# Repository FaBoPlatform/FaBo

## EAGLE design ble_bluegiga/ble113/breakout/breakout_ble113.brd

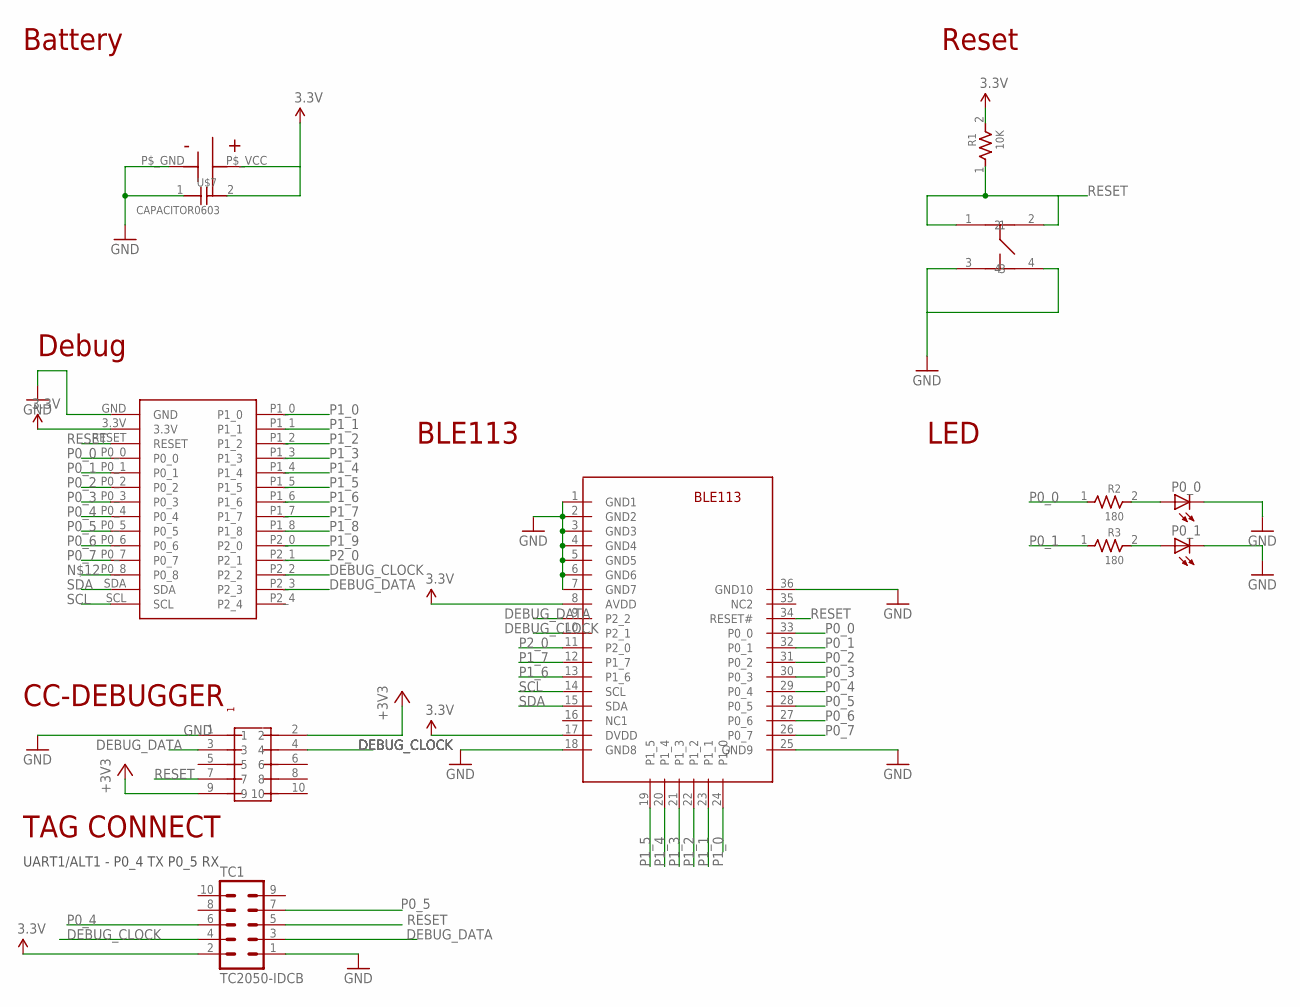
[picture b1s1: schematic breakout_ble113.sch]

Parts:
P0_0, P0_1: LEDCHIP-LED0603; CHIP-LED0603
R1: 10K; 0603
R2, R3: 180; 0603
TC1: TC2050-IDCB; TC2050-IDC
U$1: PIN-HEADER-SMT(1.27MM)2X5
U$2: BREAKOUT_BLE
U$3: BLUEGIGA-BLE113
U$4: SMTU2450-TOP; SMTU2450
U$5: SWICTH-4P(KMR2); SWITCH-4P(KMR2)
U$7: CAPACITOR0603; 0603

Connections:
3.3V: R1.2, TC1.2, U$2.3.3V, U$3.8 (AVDD), U$3.17 (DVDD), U$4.P$_VCC (+), U$7.2
+3V3: U$1.2, U$1.9
DEBUG_CLOCK: TC1.4, U$1.4, U$2.P2_2, U$3.10 (P2_1)
DEBUG_DATA: TC1.3, U$1.3, U$2.P2_3, U$3.9 (P2_2)
GND: P0_0.C, P0_1.C, TC1.1, U$1.1, U$2.GND, U$3.1 (GND1), U$3.2 (GND2), U$3.3 (GND3), U$3.4 (GND4), U$3.5 (GND5), U$3.6 (GND6), U$3.7 (GND7), U$3.18 (GND8), U$3.25 (GND9), U$3.36 (GND10), U$4.P$_GND (-), U$5.3, U$5.4, U$7.1
P0_0: R2.1, U$2.P0_0, U$3.33 (P0_0)
P0_1: R3.1, U$2.P0_1, U$3.32 (P0_1)
P0_2: U$2.P0_2, U$3.31 (P0_2)
P0_3: U$2.P0_3, U$3.30 (P0_3)
P0_4: TC1.6, U$2.P0_4, U$3.29 (P0_4)
P0_5: TC1.7, U$2.P0_5, U$3.28 (P0_5)
P0_6: U$2.P0_6, U$3.27 (P0_6)
P0_7: U$2.P0_7, U$3.26 (P0_7)
P1_0: U$2.P1_0, U$3.24 (P1_0)
P1_1: U$2.P1_1, U$3.23 (P1_1)
P1_2: U$2.P1_2, U$3.22 (P1_2)
P1_3: U$2.P1_3, U$3.21 (P1_3)
P1_4: U$2.P1_4, U$3.20 (P1_4)
P1_5: U$2.P1_5, U$3.19 (P1_5)
P1_6: U$2.P1_6, U$3.13 (P1_6)
P1_7: U$2.P1_7, U$3.12 (P1_7)
P1_8: U$2.P1_8
P1_9: U$2.P2_0
P2_0: U$2.P2_1, U$3.11 (P2_0)
R1: P0_1.A, R3.2
R2: P0_0.A, R2.2
RESET: R1.1, TC1.5, U$1.7, U$2.RESET, U$3.34 (RESET#), U$5.1, U$5.2
SCL: U$2.SCL, U$3.14 (SCL)
SDA: U$2.SDA, U$3.15 (SDA)

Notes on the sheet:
Reset
Battery
Debug
BLE113
LED
UART1/ALT1 - P0_4 TX P0_5 RX
TAG CONNECT
CC-DEBUGGER

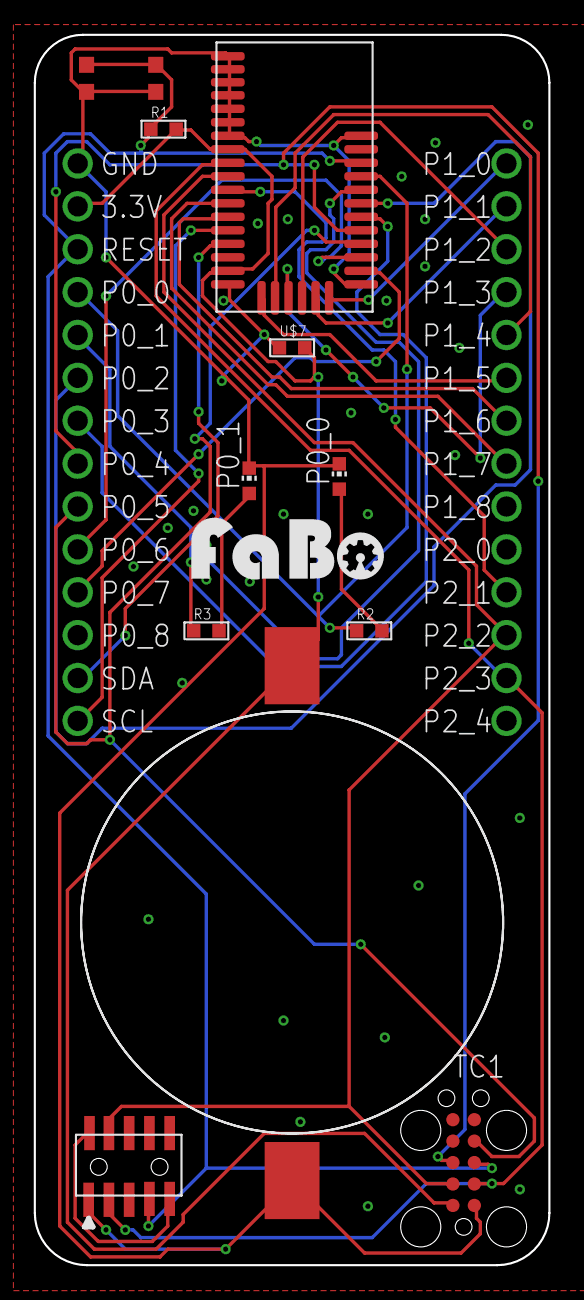
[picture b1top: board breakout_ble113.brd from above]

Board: 2 copper layers, 30.5 x 72.9 mm, 13 parts (0 on the bottom side), 27 nets.

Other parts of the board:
U$8: LOGO_FABO_M

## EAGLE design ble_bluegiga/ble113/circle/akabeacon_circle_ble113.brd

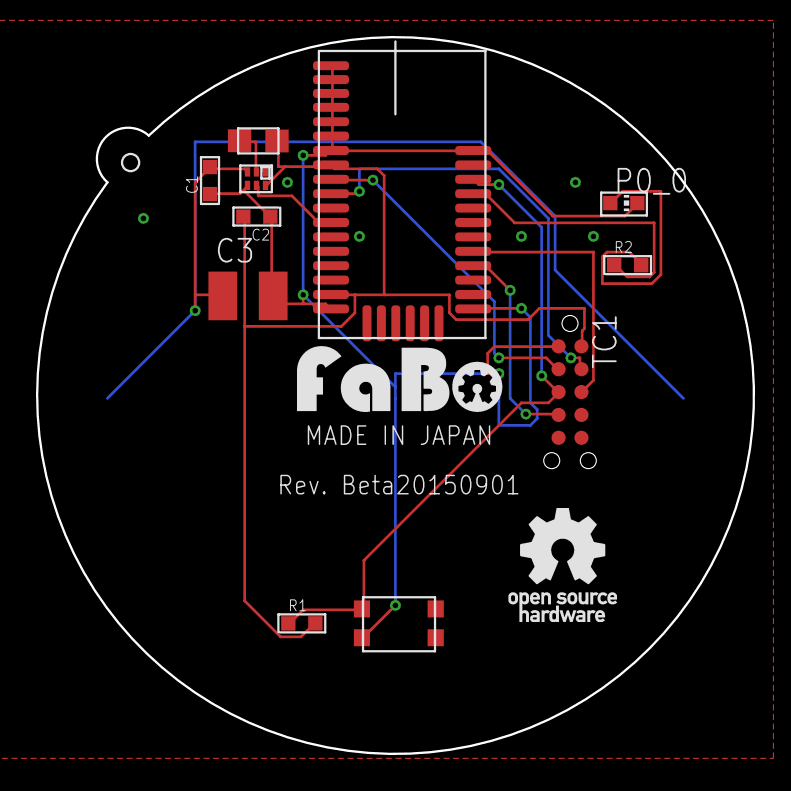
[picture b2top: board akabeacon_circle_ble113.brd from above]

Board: 2 copper layers, 39.8 x 39.8 mm, 14 parts (0 on the bottom side), 12 nets.

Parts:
C1, C2: CAPACITOR0603; 0603
C3: C3225
I1: INDUCTOR-0805
P0_0: CHIP-LED0603
R1: 10K; 0603
R2: 180; 0603
TC1: TC2050-IDC; TC2050-IDC-NL
TPS1: TI-TPS62730
U$1: CIRCLE-TYPE1; CIRCLE-TYE1-TC2030
U$2: LOGO_FABO_M
U$4: BLE113
U$5: SWICTH-4P(KMR2); SWITCH-4P(KMR2)
U$7: LOGO_OSHW_T_M

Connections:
3.3V: C2.2, I1.P$2, R1.2, TC1.2, TPS1.6, U$4.8, U$4.17
DEBUG_CLOCK: TC1.4, U$4.10
DEBUG_DATA: TC1.3, U$4.9
GND: C1.1, C2.1, C3.2, P0_0.C, TC1.1, TPS1.4, U$1.GND, U$4.1, U$4.2, U$4.3, U$4.4, U$4.5, U$4.6, U$4.7, U$4.18, U$4.25, U$4.36, U$5.3
unnamed: C1.2, C3.1, TPS1.3, U$1.PLUS1, U$1.PLUS2
unnamed: I1.P$1, TPS1.2
P0_0: R2.1, U$4.33
P0_4: TC1.6, U$4.29
P0_5: TC1.7, U$4.28
P1_7: TPS1.5, U$4.12
R2: P0_0.A, R2.2
RESET: R1.1, TC1.5, U$4.34, U$5.1

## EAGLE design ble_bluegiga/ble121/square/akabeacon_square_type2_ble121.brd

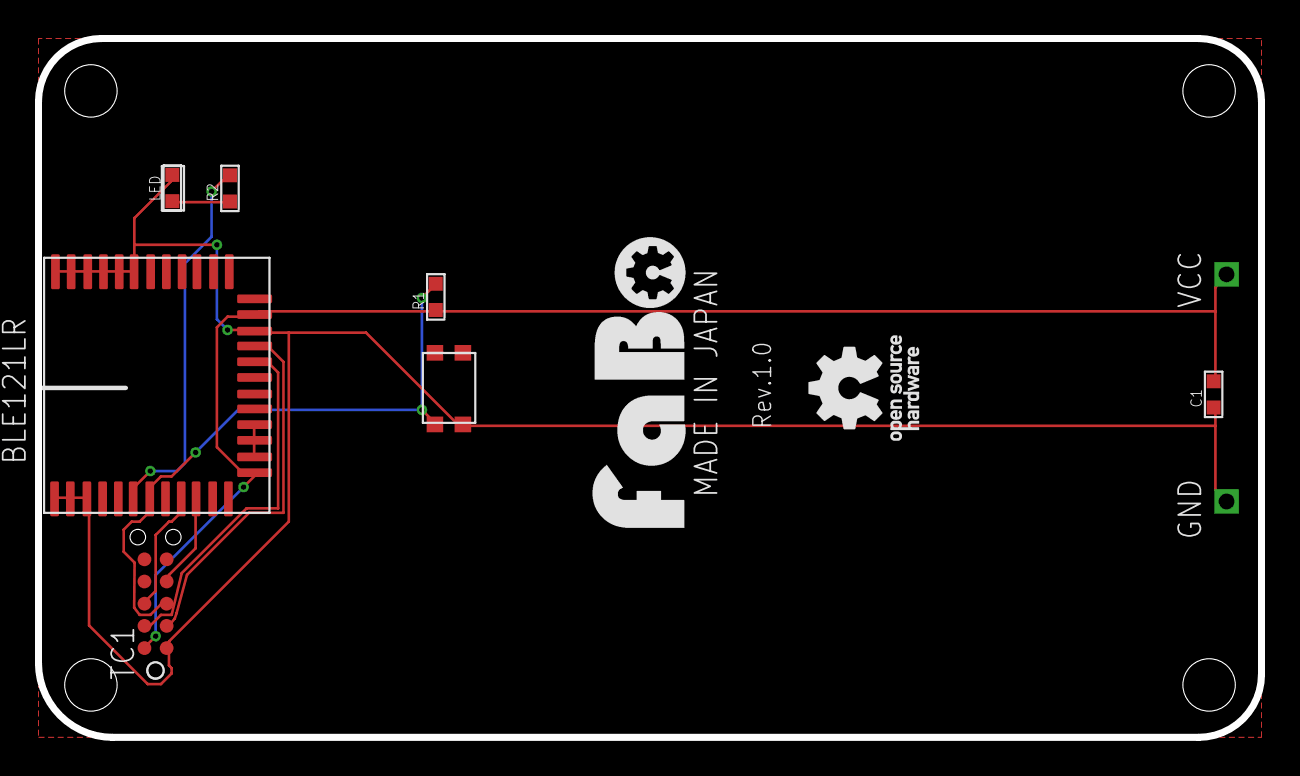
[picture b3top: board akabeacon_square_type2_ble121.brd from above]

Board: 2 copper layers, 70.0 x 40.0 mm, 8 parts (0 on the bottom side), 10 nets.

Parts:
BLE1: BLUEGIGA-BLE121LR
C1: 1u; 0603
LED: LED0603; 0603
R1, R2: 4.7K; 0603
TC1: TC2050-IDC; TC2050-IDC-NL
U$2: SQUARE-TYPE2-TC2050
U$6: SWICTH-4P(KMR2); SWITCH-4P(KMR2)

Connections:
3.3V: BLE1.13, BLE1.23, C1.2, R1.1, TC1.2, U$2.VCC
DEBUG_CLOCK: BLE1.20, TC1.4
DEBUG_DATA: BLE1.21, TC1.3
GND: BLE1.1, BLE1.2, BLE1.3, BLE1.22, BLE1.31, BLE1.32, BLE1.33, BLE1.34, BLE1.35, BLE1.36, C1.1, LED.CATHODE, TC1.1, U$2.GND, U$6.3
unnamed: LED.ANODE, R2.1
unnamed: BLE1.14, BLE1.15, BLE1.16
P0_0: BLE1.6, R2.2
P0_4: BLE1.9, TC1.6
P0_5: BLE1.10, TC1.7
RESET: BLE1.7, R1.2, TC1.5, U$6.1

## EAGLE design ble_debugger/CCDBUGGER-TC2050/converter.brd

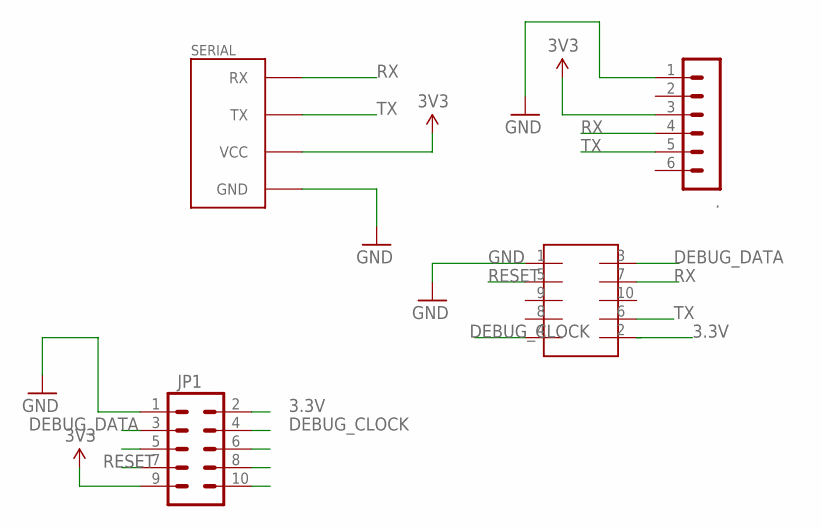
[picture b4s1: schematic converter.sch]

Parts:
.: MA06-1
JP1: M05X2SHD; 2X5-SHROUDED
SERIAL: FABO_BRICK_SERIAL-CONNECTOR_I; FABO_BRICK_SERIAL_CONNECTOR_I
U$4: TC-2050-SOCKET

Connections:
3.3V: JP1.2, U$4.2
3V3: ..3, JP1.9, SERIAL.VCC
CSN: JP1.5
DEBUG_CLOCK: JP1.4, U$4.4
DEBUG_DATA: JP1.3, U$4.3
GND: ..1, JP1.1, SERIAL.GND, U$4.1
MISO: JP1.10
MOSI: JP1.8
RESET: JP1.7, U$4.5
RX: ..4, SERIAL.RX, U$4.7
SCLK: JP1.6
TX: ..5, SERIAL.TX, U$4.6

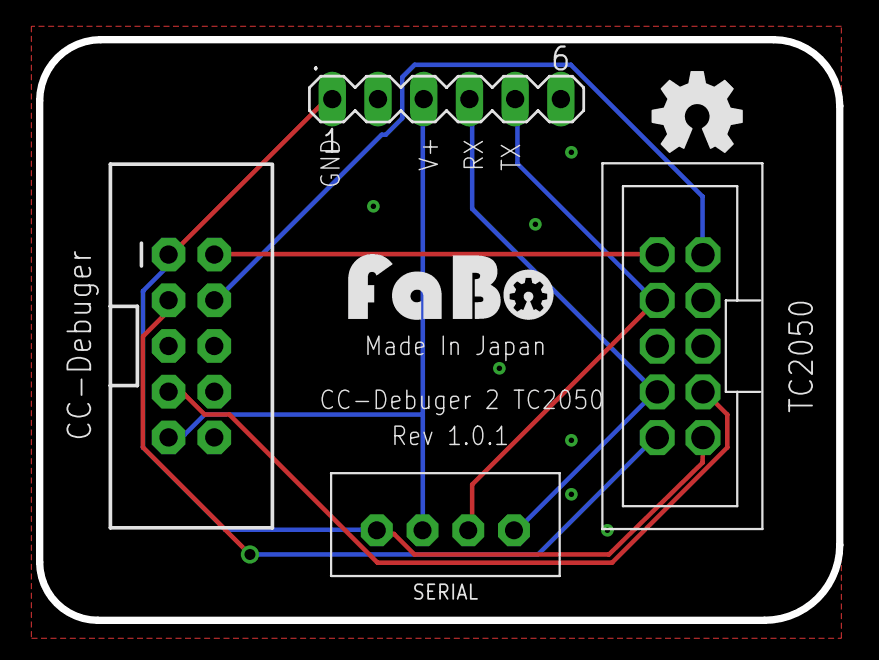
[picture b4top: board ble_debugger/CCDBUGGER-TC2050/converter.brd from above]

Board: 2 copper layers, 44.4 x 32.3 mm, 6 parts (0 on the bottom side), 8 nets.

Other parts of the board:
U$1: LOGO_FABO_M
U$2: LOGO_OSHW_M

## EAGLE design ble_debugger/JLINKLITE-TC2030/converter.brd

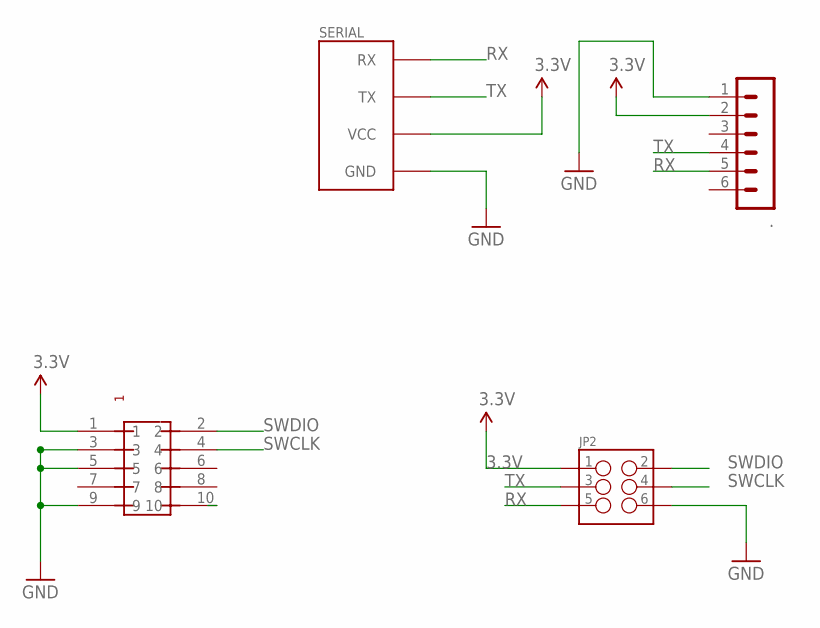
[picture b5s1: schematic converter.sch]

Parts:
.: MA06-1
JP2: M03X2; 2X3-SHROUDED
SERIAL: FABO_BRICK_SERIAL-CONNECTOR_I; FABO_BRICK_SERIAL_CONNECTOR_I
U$5: PIN-HEADER-SMT(1.27MM)2X5

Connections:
3.3V: ..2, JP2.1, SERIAL.VCC, U$5.1
GND: ..1, JP2.6, SERIAL.GND, U$5.3, U$5.5, U$5.9
RESET: U$5.10
RX: ..5, JP2.5, SERIAL.RX
SWCLK: JP2.4, U$5.4
SWDIO: JP2.2, U$5.2
TX: ..4, JP2.3, SERIAL.TX

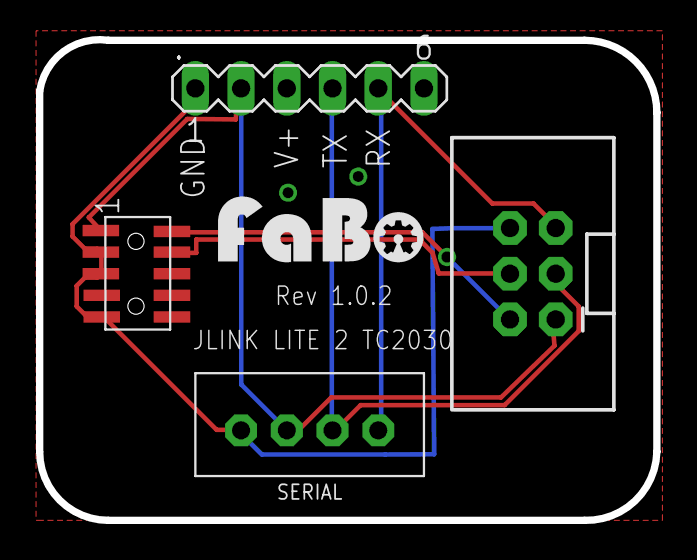
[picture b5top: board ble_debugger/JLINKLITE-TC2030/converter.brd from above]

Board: 2 copper layers, 34.3 x 26.7 mm, 5 parts (0 on the bottom side), 6 nets.

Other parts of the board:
U$1: LOGO_FABO_M

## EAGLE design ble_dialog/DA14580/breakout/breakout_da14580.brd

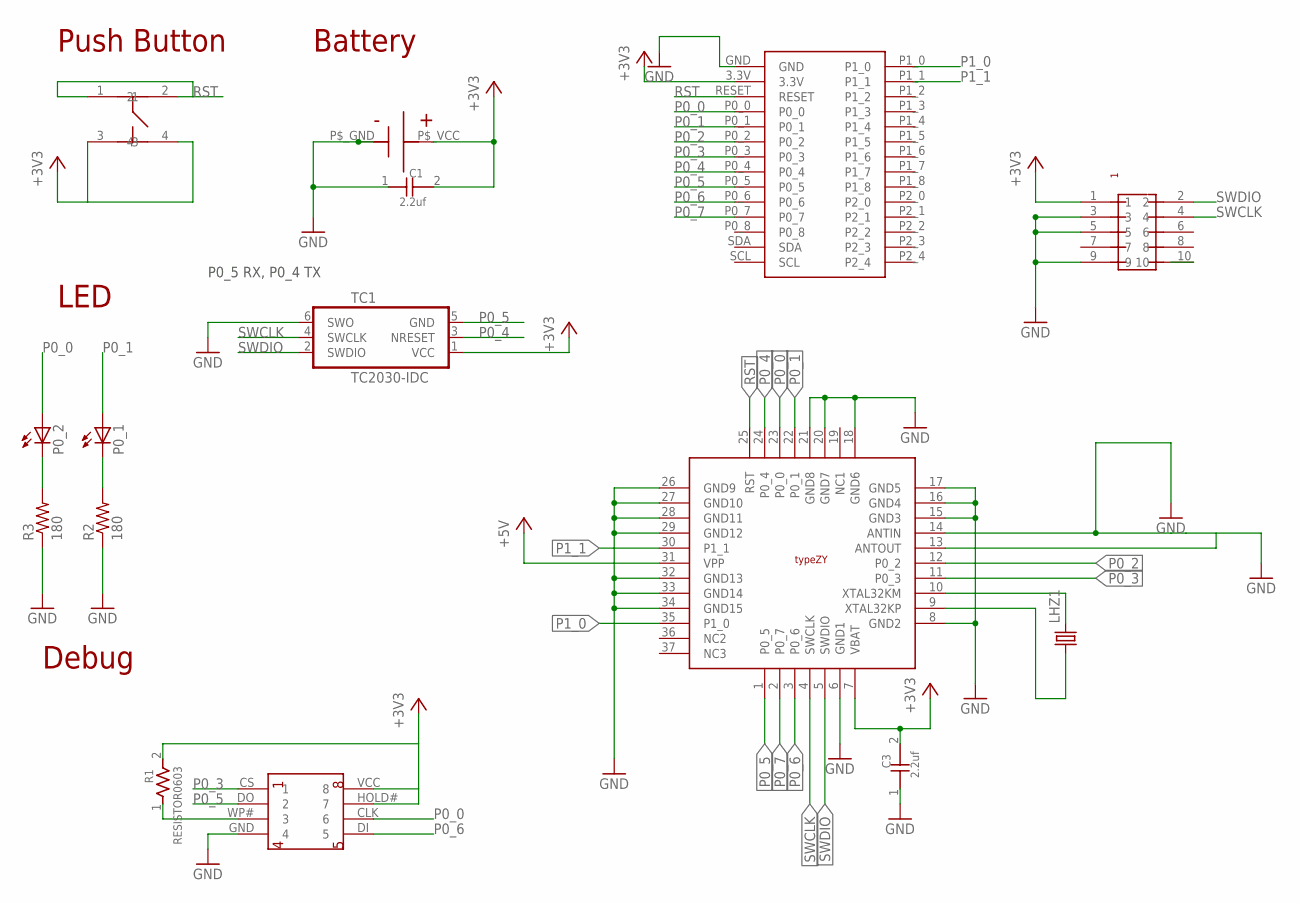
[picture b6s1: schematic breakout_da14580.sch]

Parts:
C1, C3: 2.2uf; 0603
LHZ1: FC-12M
P0_1, P0_2: LEDCHIP-LED0603; CHIP-LED0603
R1: RESISTOR0603; 0603
R2, R3: 180; 0603-RES
TC1: TC2030-IDC
U$1: MURATA-TYPEZY; MURATA_TYPEZY
U$2: BREAKOUT_BLE
U$3: SMTU2450-TOP; SMTU2450
U$5: FLASH-MEMORY-2M(WINBOND)
U$6: PIN-HEADER-SMT(1.27MM)2X5
U$7: SWICTH-4P(KMR2); SWITCH-4P(KMR2)

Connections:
+3V3: C1.2, C3.2, R1.2, TC1.1 (VCC), U$1.7 (VBAT), U$2.3.3V, U$3.P$_VCC (+), U$5.HOLD# (7), U$5.VCC (8), U$6.1, U$7.3, U$7.4
+5V: U$1.31 (VPP)
GND: C1.1, C3.1, R2.1, R3.1, TC1.6 (SWO), U$1.6 (GND1), U$1.8 (GND2), U$1.14 (ANTIN), U$1.15 (GND3), U$1.16 (GND4), U$1.17 (GND5), U$1.18 (GND6), U$1.20 (GND7), U$1.21 (GND8), U$1.26 (GND9), U$1.27 (GND10), U$1.28 (GND11), U$1.29 (GND12), U$1.32 (GND13), U$1.33 (GND14), U$1.34 (GND15), U$2.GND, U$3.P$_GND (-), U$5.GND (4), U$6.3, U$6.5, U$6.9
LED1: P0_1.C, R2.2
LED2: P0_2.C, R3.2
unnamed: R1.1, U$5.WP# (3)
P0_0: P0_2.A, U$1.23 (P0_0), U$2.P0_0, U$5.CLK (6)
P0_1: P0_1.A, U$1.22 (P0_1), U$2.P0_1
P0_2: U$1.12 (P0_2), U$2.P0_2
P0_3: U$1.11 (P0_3), U$2.P0_3, U$5.CS (1)
P0_4: TC1.3 (NRESET), U$1.24 (P0_4), U$2.P0_4
P0_5: TC1.5 (GND), U$1.1 (P0_5), U$2.P0_5, U$5.DO (2)
P0_6: U$1.3 (P0_6), U$2.P0_6, U$5.DI (5)
P0_7: U$1.2 (P0_7), U$2.P0_7
P1_0: U$1.35 (P1_0), U$2.P1_0
P1_1: U$1.30 (P1_1), U$2.P1_1
RESET: U$6.10
RST: U$1.25 (RST), U$2.RESET, U$7.1, U$7.2
SWCLK: TC1.4 (SWCLK), U$1.4 (SWCLK), U$6.4
SWDIO: TC1.2 (SWDIO), U$1.5 (SWDIO), U$6.2
XTAL32KM: LHZ1.2, U$1.10 (XTAL32KM)
XTAL32KP: LHZ1.1, U$1.9 (XTAL32KP)

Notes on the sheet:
Battery
Push Button
Debug
LED
P0_5 RX, P0_4 TX

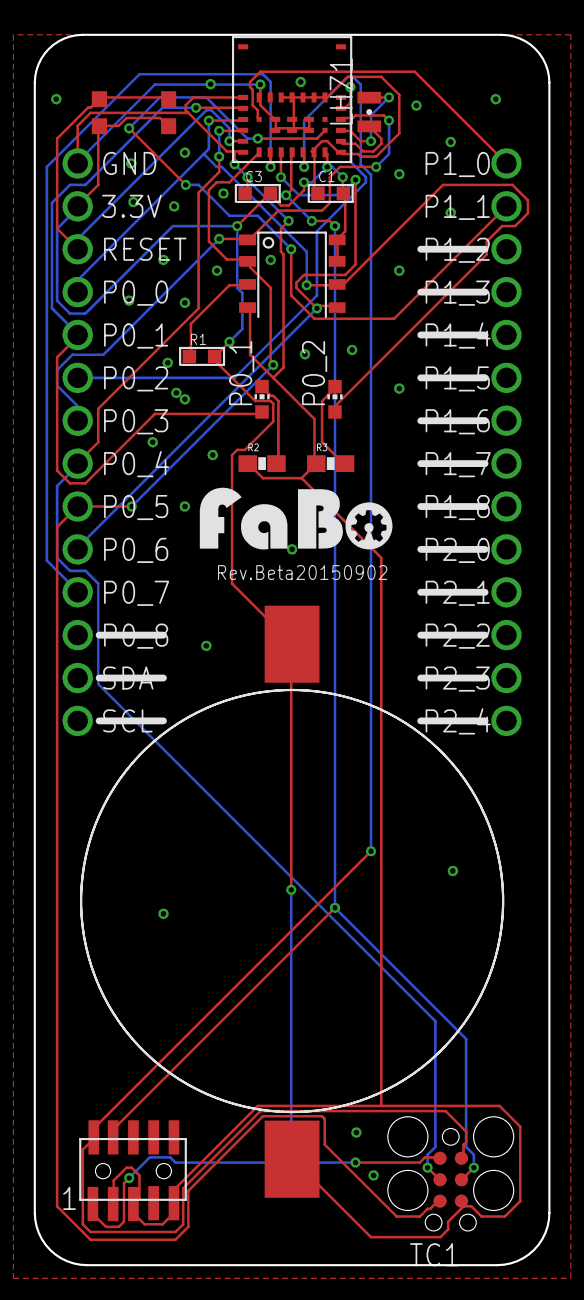
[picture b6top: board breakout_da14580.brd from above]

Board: 2 copper layers, 30.5 x 72.9 mm, 16 parts (0 on the bottom side), 20 nets.

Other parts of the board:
U$8: LOGO_FABO_M

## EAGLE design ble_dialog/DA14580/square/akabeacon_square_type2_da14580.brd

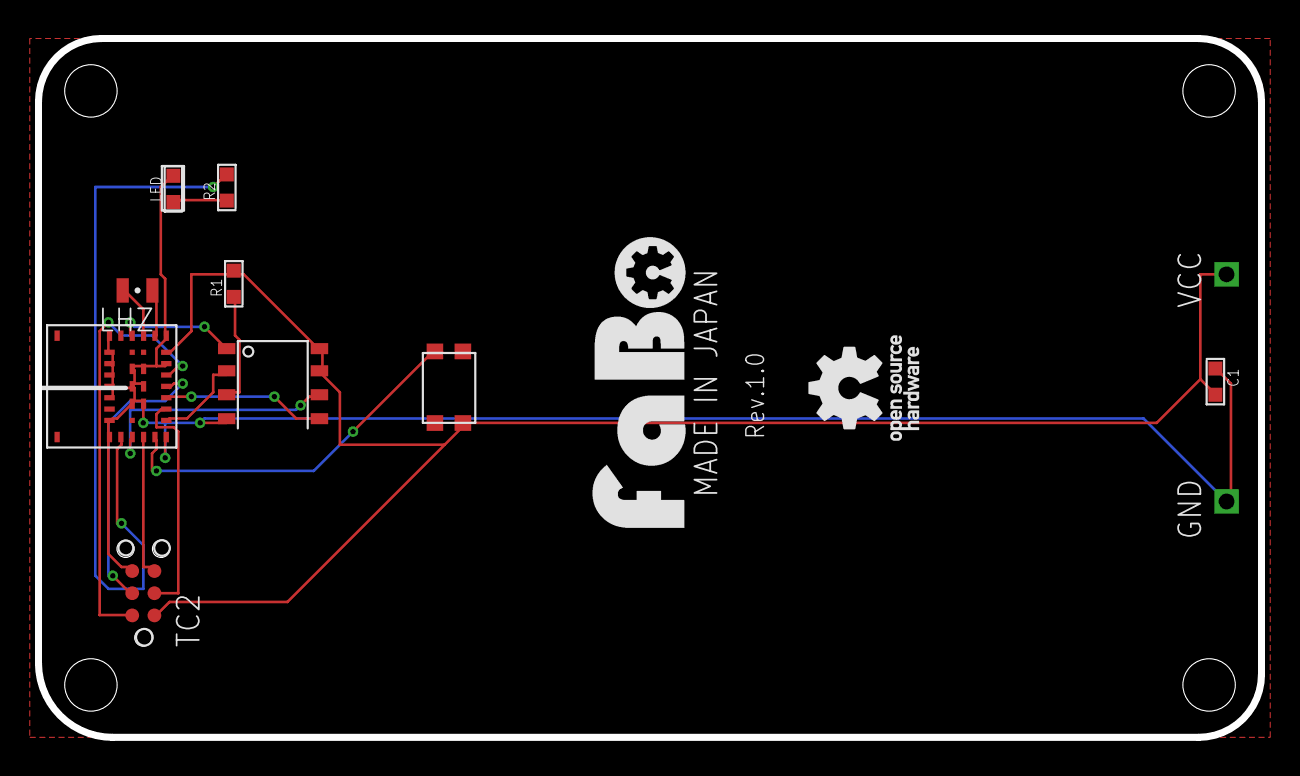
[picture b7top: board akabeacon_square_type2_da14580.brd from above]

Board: 2 copper layers, 70.0 x 40.0 mm, 10 parts (0 on the bottom side), 16 nets.

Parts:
C1: 2.2uf; 0603
LED: LED0603; 0603
LHZ: FC-12M
R1: RESISTOR0603; 0603
R2: 4.7K; 0603
TC2: TC2030-IDC-NL
U$3: FLASH-MEMORY-2M(WINBOND)
U$5: SQUARE-TYPE2-TC2030
U$7: SWICTH-4P(KMR2); SWITCH-4P(KMR2)
U$9: MURATA-TYPEZY; MURATA_TYPEZY

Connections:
+3V3: C1.2, R1.2, TC2.1, U$3.HOLD#, U$3.VCC, U$5.VCC, U$7.3, U$9.7
GND: C1.1, LED.CATHODE, TC2.6, U$3.GND, U$5.GND, U$9.6, U$9.8, U$9.13, U$9.14, U$9.15, U$9.16, U$9.17, U$9.18, U$9.20, U$9.21, U$9.26, U$9.27, U$9.28, U$9.29, U$9.32, U$9.33, U$9.34
unnamed: R1.1, U$3.WP#
unnamed: LED.ANODE, R2.1
P0_0: U$3.CLK, U$9.23
P0_1: R2.2, U$9.22
P0_3: U$3.CS, U$9.11
P0_4: TC2.5, U$9.24
P0_5: U$3.DO, U$9.1
P0_6: U$3.DI, U$9.3
P0_7: TC2.3, U$9.2
RST: U$7.2, U$9.25
SWCLK: TC2.4, U$9.4
SWDIO: TC2.2, U$9.5
XTAL32KM: LHZ.2, U$9.10
XTAL32KP: LHZ.1, U$9.9

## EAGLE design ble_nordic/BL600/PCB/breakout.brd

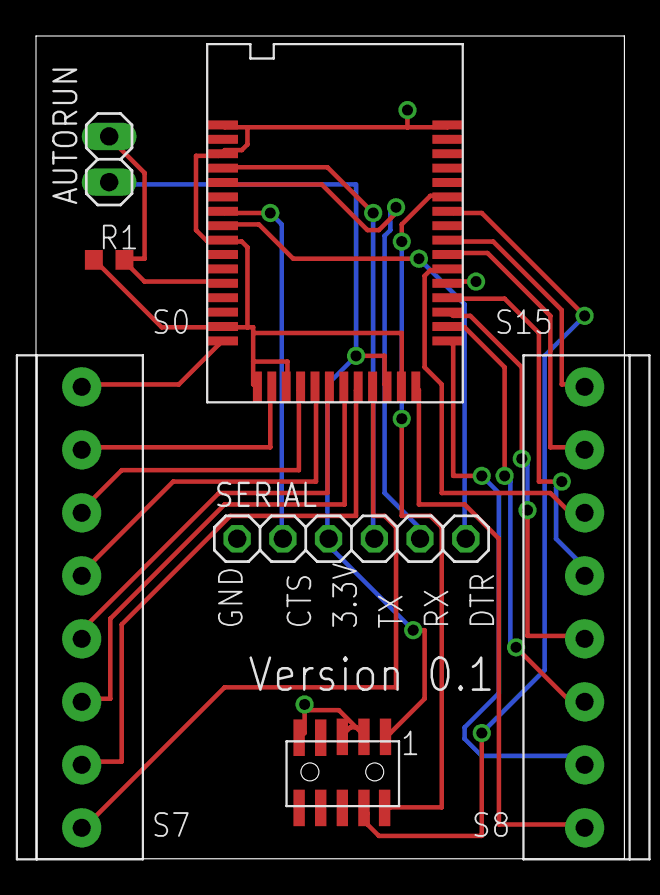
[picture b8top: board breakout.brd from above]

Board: 2 copper layers, 32.7 x 45.7 mm, 7 parts (0 on the bottom side), 25 nets.

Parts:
AUTORUN: 1X02
BL1: LAIRD-BL600
JP3, JP4: 1X08-3.5MM
R1: 10K; R0603
SERIAL: 1X06
U$1: PIN-HEADER-SMT(1.27MM)2X5

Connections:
AUTORUN: AUTORUN.2, BL1.40, R1.2
CTS: BL1.35, SERIAL.2
DTR: BL1.36, SERIAL.6
GND: BL1.1, BL1.3, BL1.11, BL1.17, BL1.28, BL1.29, BL1.31, BL1.37, BL1.43, R1.1, SERIAL.1, U$1.3, U$1.5, U$1.9
NRESET/SWDIO: BL1.22, U$1.4
RX: BL1.33, SERIAL.5
SIO_0: BL1.44, JP3.1
SIO_1: BL1.2, JP3.2
SIO_2: BL1.4, JP3.3
SIO_3: BL1.5, JP3.4
SIO_4: BL1.6, JP3.5
SIO_5: BL1.7, JP3.6
SIO_6: BL1.8, JP3.7
SIO_7: BL1.9, JP3.8
SIO_8: BL1.12, JP4.1
SIO_9: BL1.13, JP4.2
SIO_10: BL1.14, JP4.3
SIO_11: BL1.15, JP4.4
SIO_12: BL1.16, JP4.5
SIO_13: BL1.18, JP4.6
SIO_14: BL1.19, JP4.7
SIO_15: BL1.20, JP4.8
SWDCLK: BL1.23, U$1.2
TX: BL1.32, SERIAL.4
VCC: AUTORUN.1, BL1.10, SERIAL.3, U$1.1

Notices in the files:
parts and their libraries:
SparkFun: Licensing: CC v3.0 Share-Alike You are welcome to use this library for commercial purposes.
gclue: Released under the Creative Commons
gclue: https://creativecommons.org/licenses/by-sa/4.0
FaBo-Template: Released under the Creative Commons Attribution-ShareAlike 4.0 License
